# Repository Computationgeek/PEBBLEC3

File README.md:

# 🍊 FruitWorks PebbleC3

> **Built by makers, for makers.**

![PebbleC3 Board](
)

**PebbleC3** is a compact, open-source ESP32-C3 development board designed by [FruitWorks Electronics](https://github.com/fruitworkselectronics). Built as a portfolio and KiCad skill project, it packs native USB, Qwiic/STEMMA QT connectivity, and castellated edges into a small, orange form factor.

---

## ✨ Features

- **ESP32-C3-WROOM-02** — RISC-V single-core @ 160MHz, 4MB Flash, 400KB SRAM, Wi-Fi + BLE 5.0
- **Native USB** — Direct USB-C to ESP32-C3 USB (no CH340 or CP2102), supports CDC/JTAG
- **AP2112K-3.3 LDO** — 600mA, ultra-low dropout (350mV), SOT-23-5
- **Qwiic / STEMMA QT** — JST-SH 4-pin connector for plug-and-play I2C ecosystem
- **Castellated edges** — 8-pin castellated pads on each side, 2.54mm pitch, solderable directly to a carrier board
- **User LED + Power LED** — GPIO-driven user LED (IO3) and always-on power indicator
- **Boot + Reset buttons** — Standard tactile switches for programming and reset
- **Test points** — VOUT and GND test pads for bench probing
- **Open Source Hardware** — Full KiCad project, schematics, and Gerbers available

---

## 📐 Specifications

| Parameter | Value |
|---|---|
| MCU | ESP32-C3-WROOM-02 |
| Clock Speed | 160 MHz |
| Flash | 4MB |
| SRAM | 400KB |
| Connectivity | Wi-Fi 802.11 b/g/n + BLE 5.0 |
| USB | USB-C, Native USB 2.0 (CDC + JTAG) |
| Operating Voltage | 3.3V |
| Input Voltage (VIN) | 3.8V – 6V |
| Input Voltage (USB) | 5V |
| LDO Output Current | 600mA max |
| I2C | IO8 (SDA), IO10 (SCL) |
| PCB Layers | 2 |
| PCB Dimensions | ~52 x 36mm |
| PCB Color | Ember Orange |
| Finish | ENIG |

---

## 📌 Pinout

### Left Edge (J4)

| Pin | Signal | Notes |
|---|---|---|
| 1 | GND | Ground |
| 2 | 3V3 | 3.3V regulated output |
| 3 | IO4 | GPIO / ADC |
| 4 | IO5 | GPIO / ADC |
| 5 | IO6 | GPIO |
| 6 | IO7 | GPIO |
| 7 | IO8/SDA | GPIO / I2C Data |
| 8 | BOOT | GPIO9, Boot button net |

### Right Edge (J3)

| Pin | Signal | Notes |
|---|---|---|
| 1 | VIN | Raw voltage input (3.8–6V) |
| 2 | GND | Ground |
| 3 | IO0 | GPIO / ADC |
| 4 | IO1 | GPIO / ADC |
| 5 | IO2 | GPIO / ADC, strapping pin |
| 6 | IO10/SCL | GPIO / I2C Clock |
| 7 | RXD | UART RX (IO20) |
| 8 | TXD | UART TX (IO21) |

### Qwiic / STEMMA QT (J2)

| Pin | Signal |
|---|---|
| 1 | GND |
| 2 | 3.3V |
| 3 | SDA (IO8) |
| 4 | SCL (IO10) |

---

## 🧩 Bill of Materials

| Reference | Qty | Value | Footprint | Datasheet |
|---|---|---|---|---|
| C1, C2 | 2 | 1µF | C_0805_2012Metric | — |
| C3 | 1 | 100nF | C_0201_0603Metric | — |
| C4 | 1 | 10µF | C_0805_2012Metric | — |
| D1 | 1 | User LED | LED_0805_2012Metric | — |
| D2 | 1 | Power LED | LED_0805_2012Metric | — |
| D4 | 1 | 1N5819 (SOD-123W) | Nexperia_CFP3_SOD-123W | [Datasheet](http://www.vishay.com/docs/88525/1n5817.pdf) |
| J1 | 1 | USB-C 16P Receptacle | USB_C_Receptacle_GCT_USB4110 | [USB Spec](https://www.usb.org) |
| J2 | 1 | Qwiic / STEMMA QT | JST_SH_BM04B-SRSS-TB_1x04-1MP | — |
| J3 | 1 | Right Castellated Edge (8-pin) | PinHeader_1x08_P2.54mm | — |
| J4 | 1 | Left Castellated Edge (8-pin) | PinHeader_1x08_P2.54mm | — |
| R1, R2 | 2 | 5.1kΩ | R_0805_2012Metric | — |
| R3, R6 | 2 | 470Ω | R_0805_2012Metric | — |
| R4, R5 | 2 | 10kΩ | R_0805_2012Metric | — |
| SW1 | 1 | Reset Button | SW_SPST_TS-1088 | — |
| SW2 | 1 | Boot Button | SW_SPST_TS-1088 | — |
| TP1 | 1 | VOUT Test Point | TestPoint_Pad_D1.0mm | — |
| TP2 | 1 | GND Test Point | TestPoint_Pad_D1.0mm | — |
| U1 | 1 | ESP32-C3-WROOM-02 | ESP32-C3-WROOM-02 | [Datasheet](https://www.espressif.com/sites/default/files/documentation/esp32-c3-wroom-02_datasheet_en.pdf) |
| U2 | 1 | AP2112K-3.3 | SOT-23-5 | [Datasheet](https://www.diodes.com/assets/Datasheets/AP2112.pdf) |

---

## ⚡ Power

PebbleC3 can be powered two ways:

**Via USB-C** — 5V from USB → 1N5819 diode → AP2112K-3.3 LDO → 3.3V rail

**Via VIN pad** — 3.8V–6V on VIN castellation → 1N5819 → LDO → 3.3V rail

The 1N5819 Schottky diode provides OR-ing between USB and VIN — whichever is higher wins automatically. Forward drop is ~0.4V.

> ⚠️ Do not exceed 6V on VIN. AP2112K-3.3 absolute maximum input is 6V.

---

## 🔌 USB and Programming

PebbleC3 uses the ESP32-C3's **native USB** peripheral directly — no USB-to-UART bridge chip needed.

**To flash firmware:**

1. Hold **BOOT** button
2. Press and release **RESET**
3. Release **BOOT**
4. Flash using `esptool.py` or Arduino IDE

**Arduino IDE board selection:**
```
Board: ESP32C3 Dev Module
Upload Speed: 921600
USB CDC On Boot: Enabled
```
---

## 🏭 Manufacturing

Designed for JLCPCB 2-layer standard process.

| Setting | Value |
|---|---|
| Layers | 2 |
| Thickness | 1.6mm |
| Surface Finish | ENIG |
| Solder Mask | Orange |
| Silkscreen | White |
| Castellated Holes | Yes |
| Min Hole Size | 0.2mm |
| Min Clearance | 0.1mm |

> When ordering, select **"Castellated holes: Yes"** — without this JLCPCB will route through your castellation pads.

---

## 🔓 License

This project is **Open Source Hardware** licensed under the [CERN-OHL-P v2](https://ohwr.org/cern_ohl_p_v2.txt).

You are free to use, modify, and manufacture this design. Attribution to **FruitWorks Electronics** appreciated.

---

*Built by makers, for makers.*

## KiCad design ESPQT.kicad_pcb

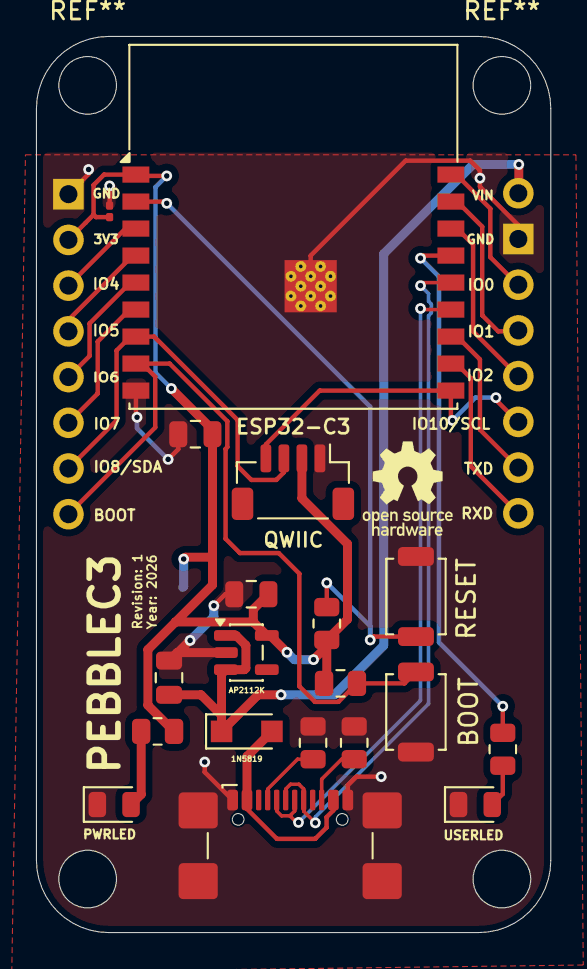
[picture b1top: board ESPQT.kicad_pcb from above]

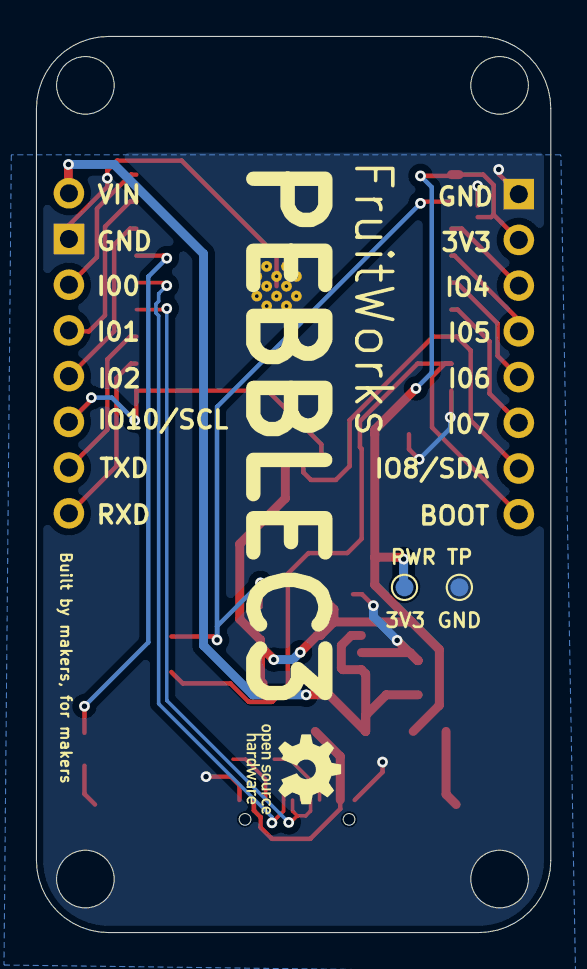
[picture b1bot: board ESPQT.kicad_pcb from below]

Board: 2 copper layers, 28.6 x 49.8 mm, 23 parts (2 on the bottom side), 24 nets.

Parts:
C1, C2: 1uF; C_0805_2012Metric
C3: 100nF; C_0201_0603Metric
C4: 10uF; C_0805_2012Metric
D1: USERLED; LED_0805_2012Metric
D2: PWRLED; LED_0805_2012Metric
D4: 1N5819; Nexperia_CFP3_SOD-123W
J1: USB2.0_C_16P; USB_C_Receptacle_GCT_USB4110
J2: QWIIC; JST_SH_BM04B-SRSS-TB_1x04-1MP_P1.00mm_Vertical
J3: Right_Edges; PinHeader_1x08_P2.54mm_Vertical_Mod
J4: Left_Edge; PinHeader_1x08_P2.54mm_Vertical_Mod
R1, R2: 5.1K; R_0805_2012Metric
R3, R6: 470; R_0805_2012Metric
R4, R5: 10K; R_0805_2012Metric
SW1: RESET; SW_SPST_TS-1088-xR020
SW2: BOOT; SW_SPST_TS-1088-xR020
TP1: 3V3; TestPoint_Pad_D1.0mm
TP2: GND; TestPoint_Pad_D1.0mm
U1: ESP32-C3; ESP32-C3-WROOM-02
U2: AP2112K; SOT-23-5

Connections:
+3.3V: C2.1, C3.1, C4.1, J2.2, J4.2, R4.1, R5.1, R6.1, TP1.1 (1_1), U1.1 (3V3), U2.5 (VOUT)
/BOOT: J4.8, R5.2, SW2.2, U1.8 (IO9)
/IO0: J3.3, U1.18 (IO0)
/IO1: J3.4, U1.17 (IO1)
/IO2: J3.5, U1.16 (IO2)
/IO4: J4.3, U1.3 (IO4)
/IO5: J4.4, U1.4 (IO5)
/IO6: J4.5, U1.5 (IO6)
/IO7: J4.6, U1.6 (IO7)
/IO8/SDA: J2.3, J4.7, U1.7 (IO8)
/IO10/SCL: J2.4, J3.6, U1.10 (IO10)
/LED: R3.1, U1.15 (IO3)
/RXD: J3.8, U1.11 (IO20/RXD)
/TXD: J3.7, U1.12 (IO21/TXD)
/USB D+: J1.A6 (D+), J1.B6 (D+), U1.14 (IO19)
/USB D-: J1.A7 (D-), J1.B7 (D-), U1.13 (IO18)
/VIN: C1.1, D4.1 (K), J3.1, U2.1 (VIN), U2.3 (EN)
GND: C1.2, C2.2, C3.2, C4.2, D1.1 (K), D2.1 (K), J1.A1 (GND), J1.A12 (GND), J1.B1 (GND), J1.B12 (GND), J1.SH (SHIELD), J2.1, J3.2, J4.1, R1.2, R2.2, SW1.1, SW2.1, TP2.1 (1_1), U1.9 (GND), U1.19 (GND), U2.2 (GND)
unnamed: D1.2 (A), R3.2
unnamed: D2.2 (A), R6.2
unnamed: D4.2 (A), J1.A4 (VBUS), J1.A9 (VBUS), J1.B4 (VBUS), J1.B9 (VBUS)
unnamed: J1.A5 (CC1), R1.1
unnamed: J1.B5 (CC2), R2.1
unnamed: R4.2, SW1.2, U1.2 (EN)
